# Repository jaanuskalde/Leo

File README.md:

Leo
===

Tech-thing Leo board. Arduino Leonardo clone.

Useful for data logging.

Features
--------
* Small size but 100% headers are the same
* Micro, mini or B USB
* All headers are servo headers
* With selectable voltages
* Micro SD card
* Real time clock onboard
* Analog referance for more precise logging
* External watchdog timer
* 5V or 3v3 selectable

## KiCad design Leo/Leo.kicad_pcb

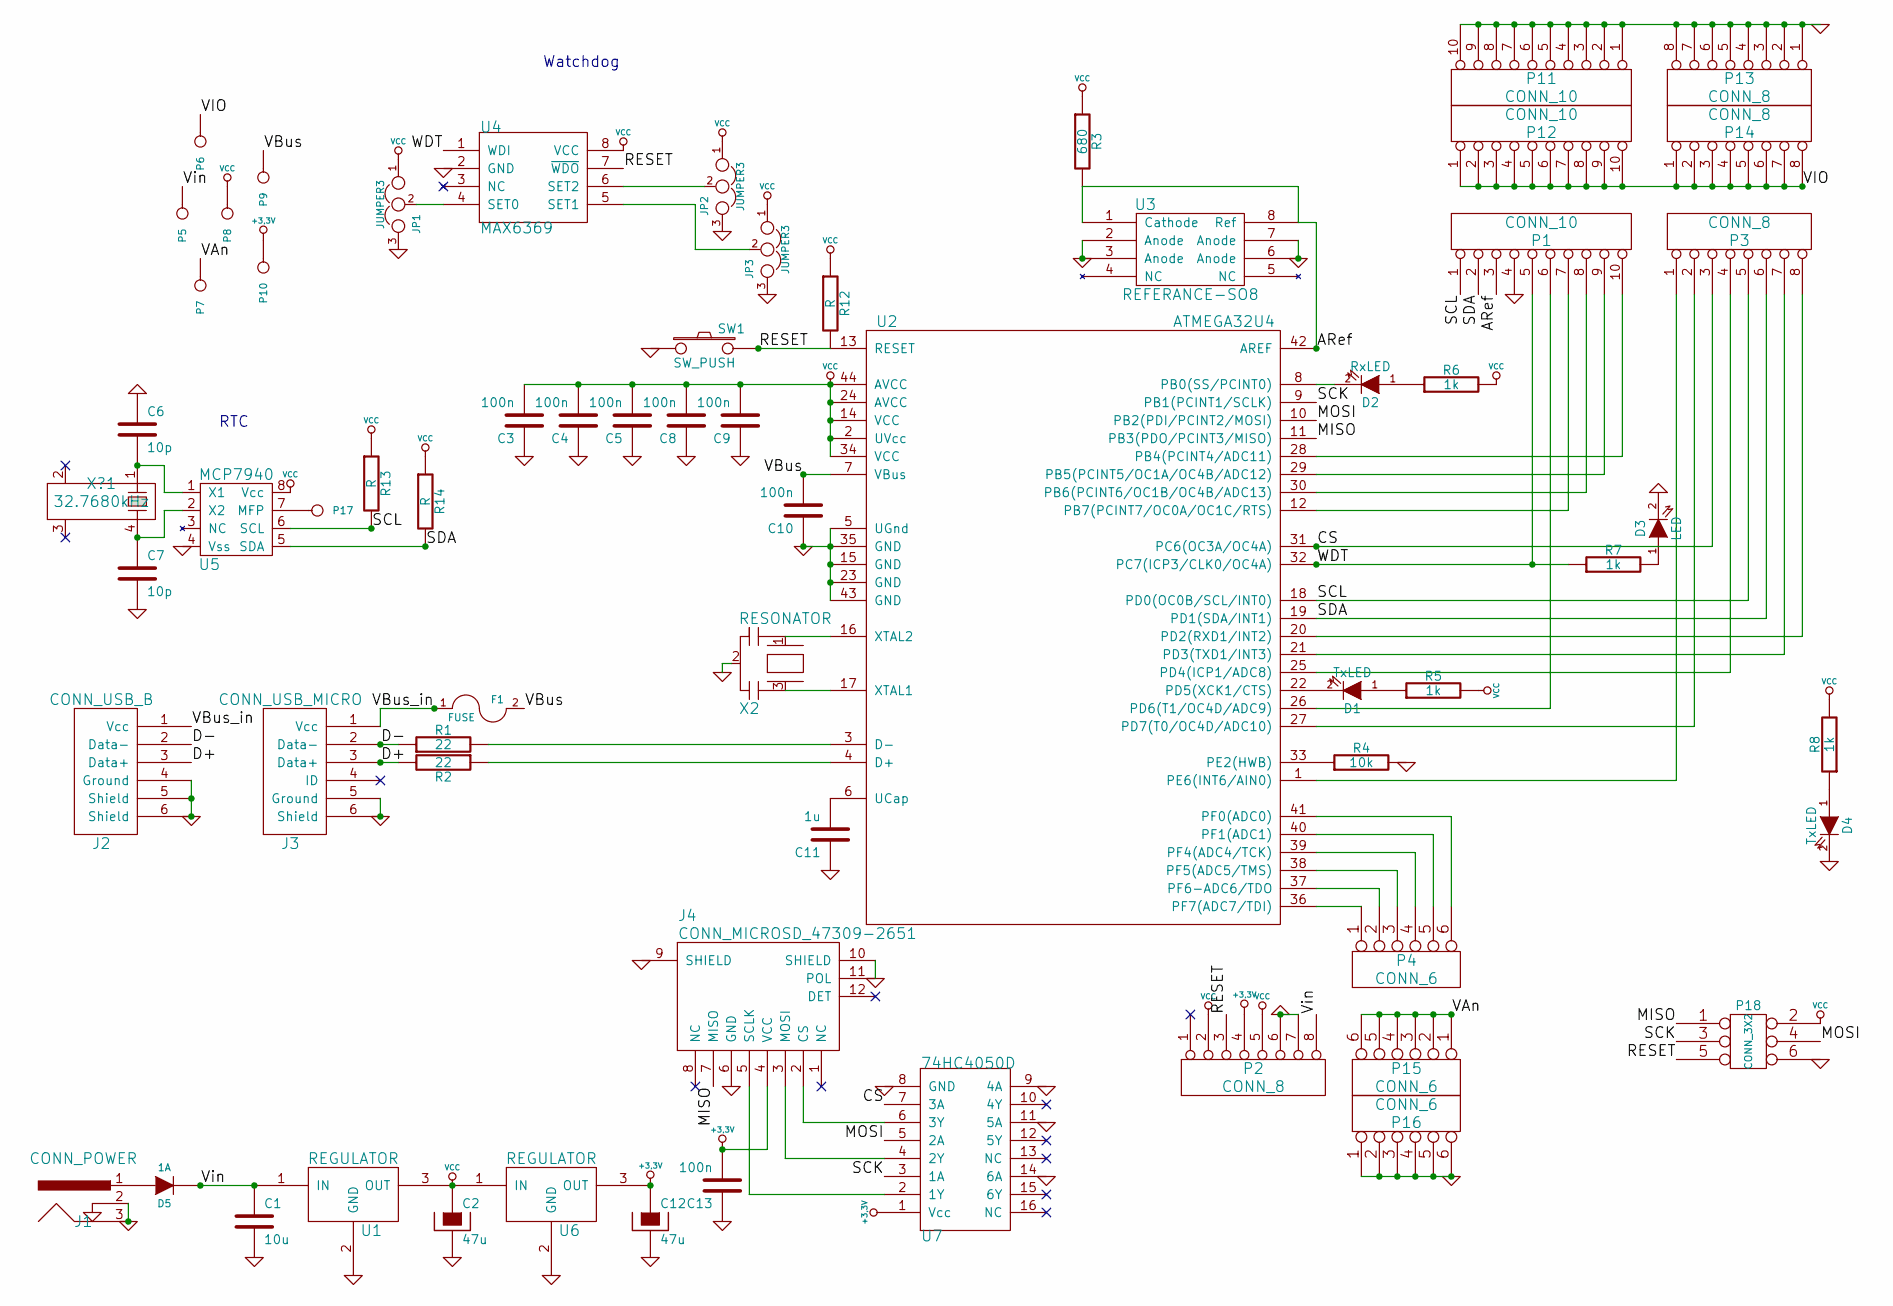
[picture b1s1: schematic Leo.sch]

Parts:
C1: 10u
C2, C12: 47u
C3, C4, C5, C8, C9, C10, C13: 100n
C6, C7: 10p
C11: 1u
D1, D4: TxLED
D2: RxLED
D3: LED
D5: 1A
F1: FUSE
J1: CONN_POWER
J2: CONN_USB_B
J3: CONN_USB_MICRO
J4: CONN_MICROSD_47309-2651
JP1, JP2, JP3: JUMPER3
P1: CONN_10
P2, P3: CONN_8
P4, P15, P16: CONN_6
P5, P6, P7, P8, P9, P10, P17: CONN_1
P11, P12: CONN_10
P13, P14: CONN_8
P18: CONN_3X2
R1, R2: 22
R3: 680
R4: 10k
R5, R6, R7, R8: 1k
R12, R13, R14: R
SW1: SW_PUSH
U1, U6: REGULATOR
U2: ATMEGA32U4
U3: REFERANCE-SO8
U4: MAX6369
U5: MCP7940
U7: 74HC4050D
X2: RESONATOR
X?1: 32.7680kHz

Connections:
+3.3V: C12.1, C13.2, J4.4 (VCC), P2.4, P10.1, U6.3 (OUT), U7.1 (Vcc)
/ARef: P1.3, R3.2, U2.42 (AREF), U3.1 (Cathode), U3.8 (Ref)
/CS: P3.3, U2.31 (PC6(OC3A/OC4A)), U7.7 (3A)
/D+: J2.3 (Data+), J3.3 (Data+), R2.2
/D-: J2.2 (Data-), J3.2 (Data-), R1.1
/MISO: J4.7 (MISO), P18.1, U2.11 (PB3(PDO/PCINT3/MISO))
/MOSI: P18.4, U2.10 (PB2(PDI/PCINT2/MOSI)), U7.5 (2A)
/RESET: P2.3, P18.5, R12.2, SW1.2, U2.13 (RESET), U4.7 (~WDO)
/SCK: P18.3, U2.9 (PB1(PCINT1/SCLK)), U7.3 (1A)
/SCL: P1.1, P3.5, R13.2, U2.18 (PD0(OC0B/SCL/INT0)), U5.6 (SCL)
/SDA: P1.2, P3.6, R14.2, U2.19 (PD1(SDA/INT1)), U5.5 (SDA)
/VAn: P7.1, P15.1, P15.2, P15.3, P15.4, P15.5, P15.6
/VBus: C10.2, F1.2, P9.1, U2.7 (VBus)
/VBus_in: F1.1, J2.1 (Vcc), J3.1 (Vcc)
/VIO: P6.1, P12.1, P12.2, P12.3, P12.4, P12.5, P12.6, P12.7, P12.8, P12.9, P12.10, P14.1, P14.2, P14.3, P14.4, P14.5, P14.6, P14.7, P14.8
/Vin: C1.1, D5.1 (K), P2.8, P5.1, U1.1 (IN)
/WDT: P1.5, R7.1, U2.32 (PC7(ICP3/CLK0/OC4A)), U4.1 (WDI)
GND: C1.2, C2.2, C3.1, C4.1, C5.1, C6.1, C7.2, C8.1, C9.1, C10.1, C11.1, C12.2, C13.1, D3.2 (K), D4.2 (K), J1.2, J1.3, J2.4 (Ground), J2.5 (Shield), J2.6 (Shield), J3.5 (Ground), J3.6 (Shield), J4.6 (GND), J4.9 (SHIELD), J4.10 (SHIELD), J4.11 (POL), JP1.3, JP2.3, JP3.3, P1.4, P2.6, P2.7, P11.1, P11.2, P11.3, P11.4, P11.5, P11.6, P11.7, P11.8, P11.9, P11.10, P13.1, P13.2, P13.3, P13.4, P13.5, P13.6, P13.7, P13.8, P16.1, P16.2, P16.3, P16.4, P16.5, P16.6, P18.6, R4.2, SW1.1, U1.2 (GND), U2.5 (UGnd), U2.15 (GND), U2.23 (GND), U2.35 (GND), U2.43 (GND), U3.2 (Anode), U3.3 (Anode), U3.6 (Anode), U3.7 (Anode), U4.2 (GND), U5.4 (Vss), U6.2 (GND), U7.8 (GND), U7.9 (4A), U7.11 (5A), U7.14 (6A), X2.2
unnamed: D4.1 (A), R8.1
unnamed: U2.16 (XTAL2), X2.1
unnamed: U2.17 (XTAL1), X2.3
unnamed: D3.1 (A), R7.2
unnamed: D1.1 (A), R5.1
unnamed: D1.2 (K), U2.22 (PD5(XCK1/CTS))
unnamed: C6.2, U5.1 (X1), X?1.1
unnamed: C7.1, U5.2 (X2), X?1.4
unnamed: P1.6, U2.26 (PD6(T1/OC4D/ADC9))
unnamed: P17.1, U5.7 (MFP)
unnamed: D2.2 (K), U2.8 (PB0(SS/PCINT0))
unnamed: D2.1 (A), R6.1
unnamed: P1.7, U2.12 (PB7(PCINT7/OC0A/OC1C/RTS))
unnamed: P1.10, U2.28 (PB4(PCINT4/ADC11))
unnamed: P1.9, U2.29 (PB5(PCINT5/OC1A/OC4B/ADC12))
unnamed: P1.8, U2.30 (PB6(PCINT6/OC1B/OC4B/ADC13))
unnamed: P4.6, U2.41 (PF0(ADC0))
unnamed: P4.1, U2.36 (PF7(ADC7/TDI))
unnamed: P4.2, U2.37 (PF6-ADC6/TDO)
unnamed: P4.3, U2.38 (PF5(ADC5/TMS))
unnamed: P4.4, U2.39 (PF4(ADC4/TCK))
unnamed: P4.5, U2.40 (PF1(ADC1))
unnamed: P3.1, U2.1 (PE6(INT6/AIN0))
unnamed: R4.1, U2.33 (PE2(HWB))
unnamed: P3.8, U2.20 (PD2(RXD1/INT2))
unnamed: P3.7, U2.21 (PD3(TXD1/INT3))
unnamed: P3.4, U2.25 (PD4(ICP1/ADC8))
unnamed: P3.2, U2.27 (PD7(T0/OC4D/ADC10))
unnamed: J4.2 (CS), U7.6 (3Y)
unnamed: J4.3 (MOSI), U7.4 (2Y)
unnamed: J4.5 (SCLK), U7.2 (1Y)
unnamed: D5.2 (A), J1.1
unnamed: JP2.2, U4.6 (SET2)
unnamed: JP3.2, U4.5 (SET1)
unnamed: JP1.2, U4.4 (SET0)
unnamed: R2.1, U2.4 (D+)
unnamed: R1.2, U2.3 (D-)
unnamed: C11.2, U2.6 (UCap)
VCC: C2.1, C3.2, C4.2, C5.2, C8.2, C9.2, JP1.1, JP2.1, JP3.1, P2.2, P2.5, P8.1, P18.2, R3.1, R5.2, R6.2, R8.2, R12.1, R13.1, R14.1, U1.3 (OUT), U2.2 (UVcc), U2.14 (VCC), U2.24 (AVCC), U2.34 (VCC), U2.44 (AVCC), U4.8 (VCC), U5.8 (Vcc), U6.1 (IN)

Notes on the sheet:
Watchdog
RTC

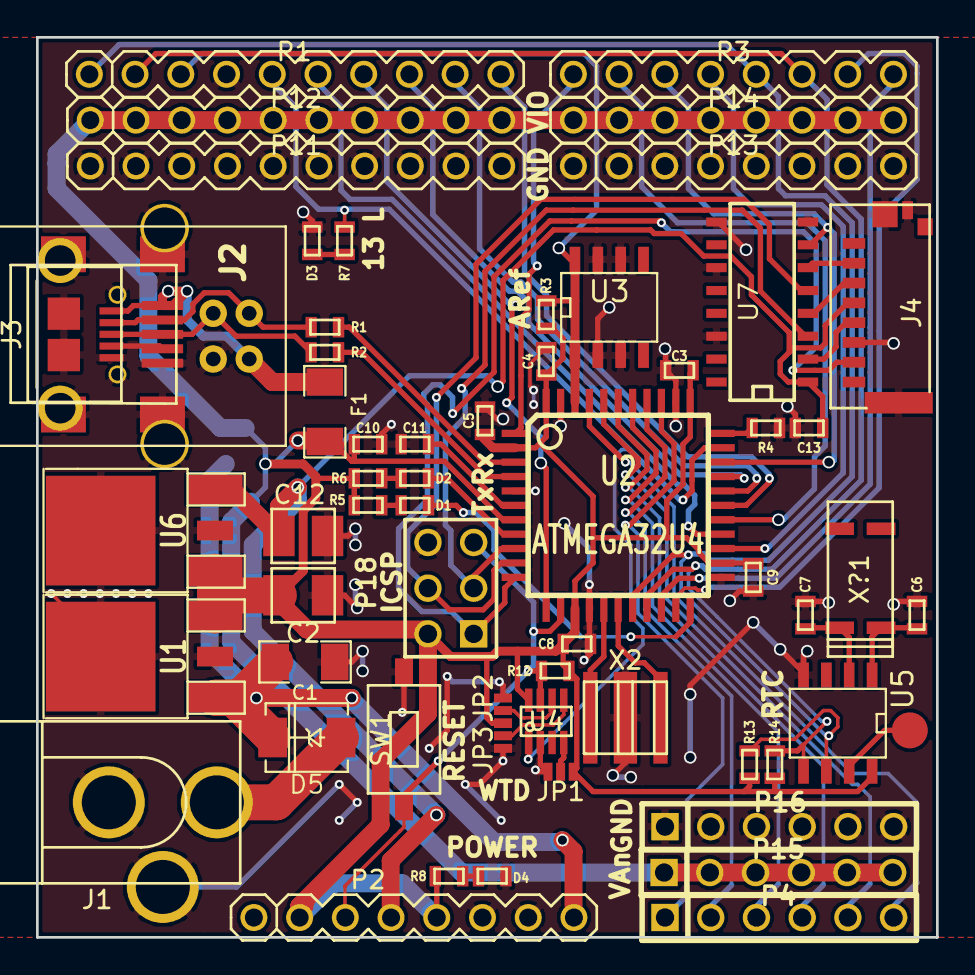
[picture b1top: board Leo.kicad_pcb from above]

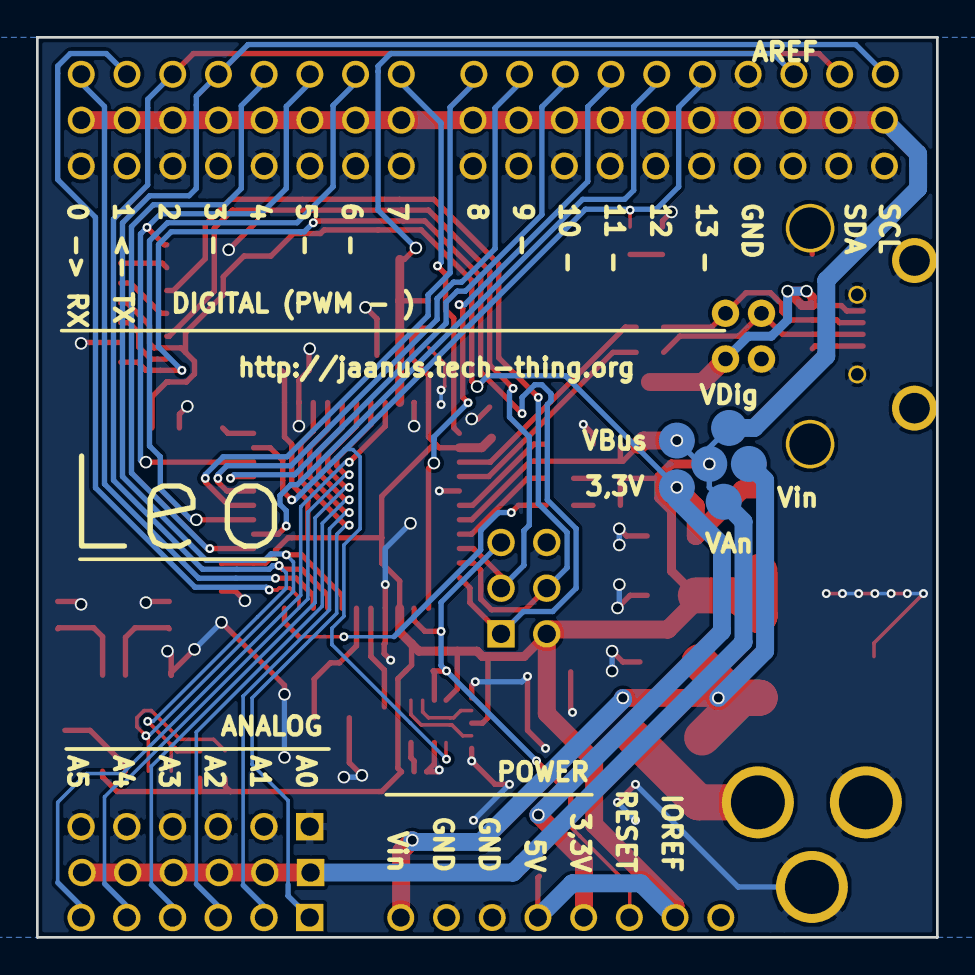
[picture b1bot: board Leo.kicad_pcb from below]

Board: 2 copper layers, 50.0 x 50.0 mm, 65 parts (6 on the bottom side), 57 nets.

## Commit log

2013-06-28 Version 1.0, first one to be manufactured, with some known bugs.
2013-07-09 Fixed MAX pinout, header spacing and silkscreen
2013-07-09 featuures
